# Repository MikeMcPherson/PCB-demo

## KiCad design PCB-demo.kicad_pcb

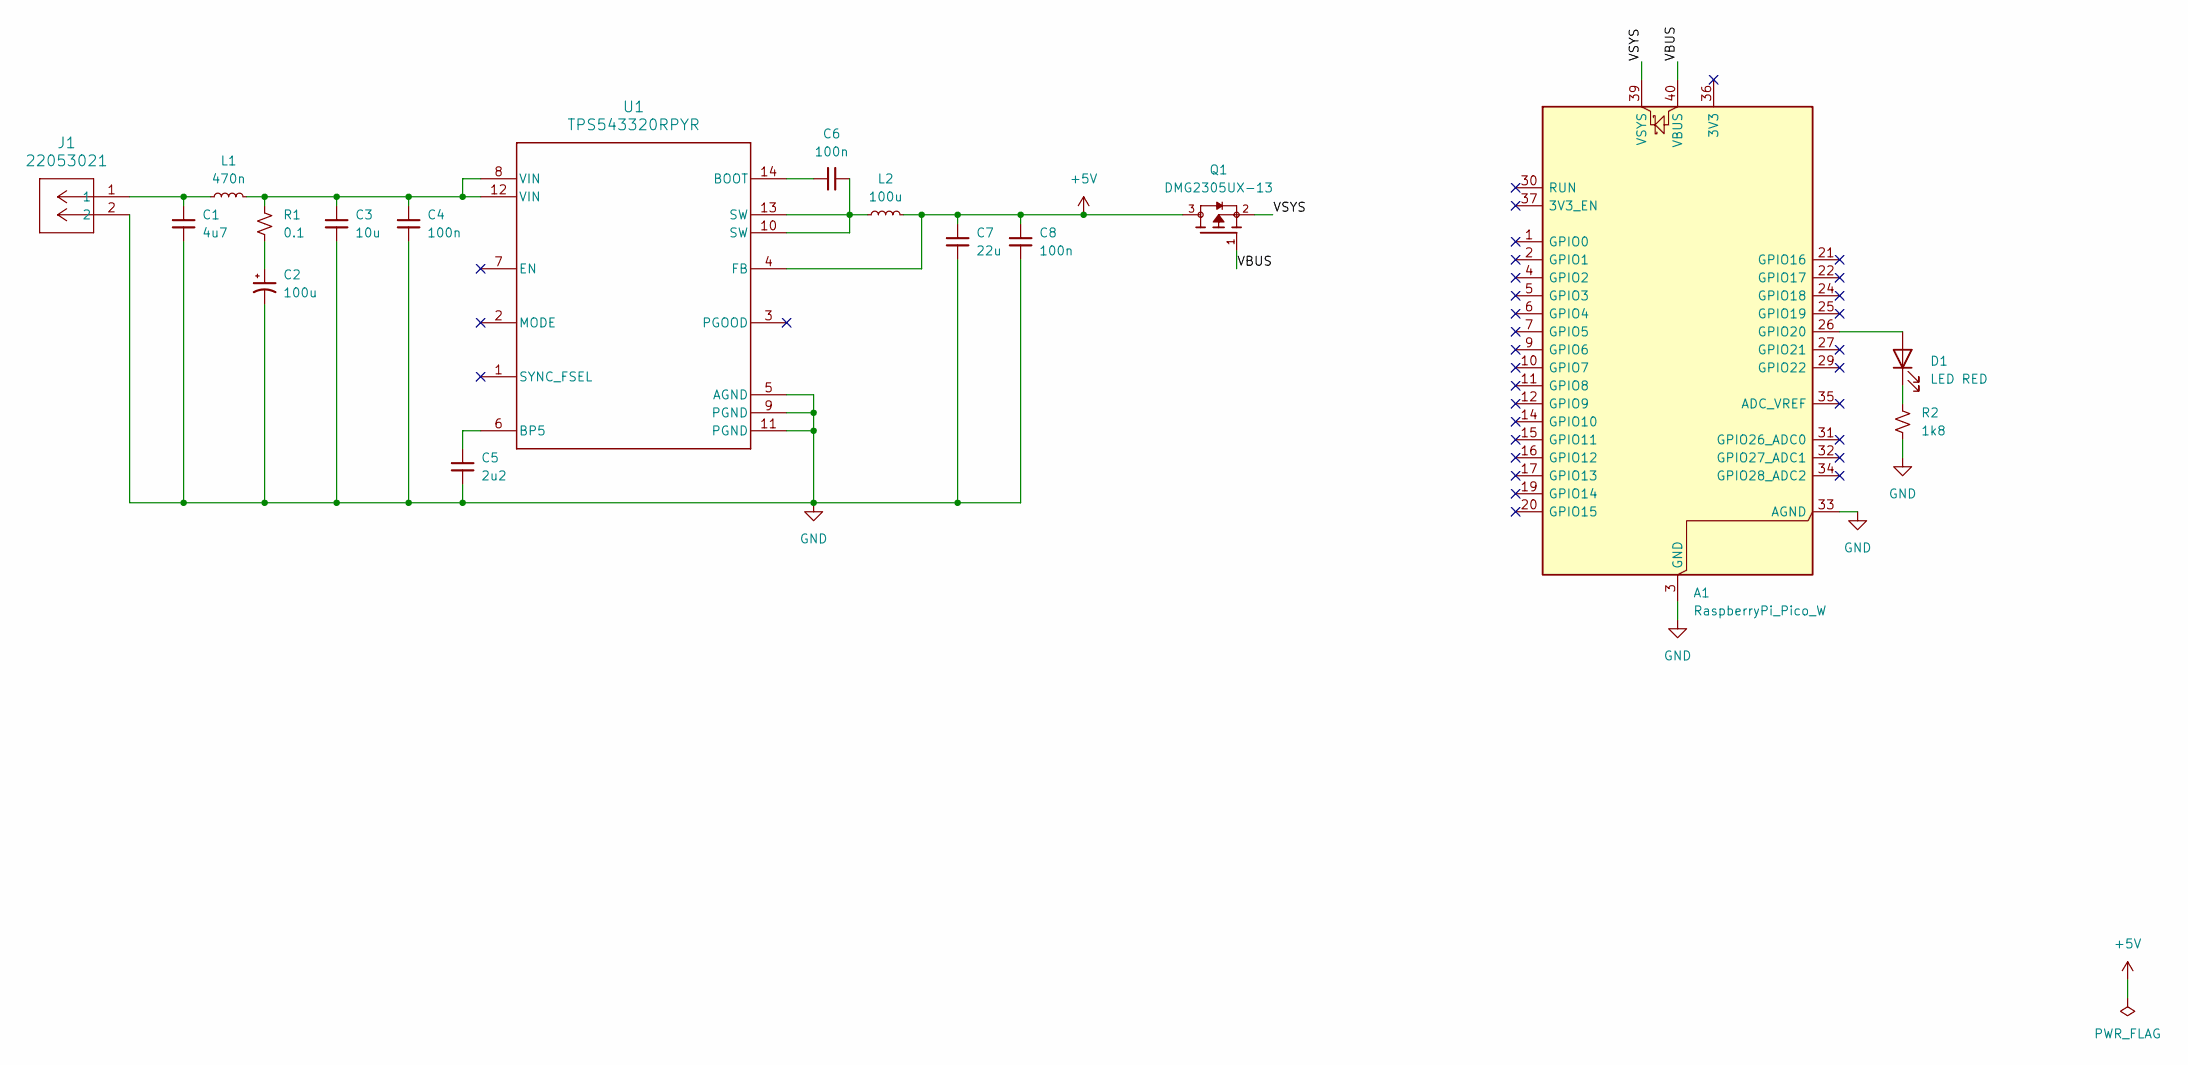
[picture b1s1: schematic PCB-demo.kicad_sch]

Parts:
A1: RaspberryPi_Pico_W; RaspberryPi_Pico_W_SMD_HandSolder
C1: 4u7; C_0603_1608Metric
C2: 100u; C_0603_1608Metric
C3: 10u; C_0603_1608Metric
C4, C6: 100n; C_0603_1608Metric
C5: 2u2; C_0603_1608Metric
C7: 22u; C_0603_1608Metric
C8: 100n; CP_Elec_10x10
D1: LED RED; LED_0603_1608Metric
J1: 22053021; CONN_A-7478-02A_MOL
L1: 470n; L_0603_1608Metric
L2: 100u; L_12x12mm_H6mm
Q1: DMG2305UX-13; SOT91P240X110-3N; PARTREV 09/2018
R1: 0.1; R_0603_1608Metric
R2: 1k8; R_0603_1608Metric
U1: TPS543320RPYR; RPY0014A-MFG

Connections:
+5V: C7.1, C8.1, L2.2, Q1.3, U1.4 (FB)
/VBUS: A1.40 (VBUS), Q1.1
/VSYS: A1.39 (VSYS), Q1.2
GND: A1.3 (GND), A1.8 (GND), A1.13 (GND), A1.18 (GND), A1.23 (GND), A1.28 (GND), A1.33 (AGND), A1.38 (GND), C1.2, C2.2, C3.2, C4.2, C5.2, C7.2, C8.2, J1.2, R2.2, U1.5 (AGND), U1.9 (PGND), U1.11 (PGND)
unnamed: A1.26 (GPIO20), D1.2 (A)
unnamed: C1.1, J1.1, L1.1
unnamed: C2.1, R1.2
unnamed: C3.1, C4.1, L1.2, R1.1, U1.8 (VIN), U1.12 (VIN)
unnamed: C6.2, L2.1, U1.10 (SW), U1.13 (SW)
unnamed: D1.1 (K), R2.1
unnamed: C6.1, U1.14 (BOOT)
unnamed: C5.1, U1.6 (BP5)

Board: 2 copper layers, 17 parts (0 on the bottom side), 12 nets, no tracks yet.
